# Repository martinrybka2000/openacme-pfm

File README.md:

# OpenACME‑PFM

**Open** **AC** **M**ains **E**nergy — **PFM** (Power Factor Meter).

An open-source **power quality meter** for AC installations. It measures voltage, current, power (active / reactive / apparent), frequency, power factors and THD, and exposes the results over Ethernet and Modbus, with PQDIF export for professional analysis tools.

> ⚠️ **DANGER — MAINS VOLTAGE.**
> This project connects directly to 230 V AC mains. Building, flashing, testing or using it can **injure or kill you** and can **start a fire**. Read [`docs/user-guide/safety.md`](docs/user-guide/safety.md) before touching any hardware. You build and use everything here **entirely at your own risk**.

---

## Status

🚧 **V2.0 — under development.**

The V1.0 single-board prototype (the basis of my master's thesis) is preserved **as-is** in [`v1.0/`](v1.0/) for reference only — no cleanup, no support.

## What it measures

- RMS voltage and current (total and fundamental)
- Active `P`, reactive `Q`, non-active `N` and apparent `S` power
- Fundamental components `P1`, `Q1`, `S1`
- Power factors: `PF` (true), `DPF` (displacement), `DF` (distortion)
- `THD` of voltage and current
- Frequency and phase angle (SOGI-PLL grid synchronisation)
- 10-cycle aggregation window (IEC 61000-4-7), loosely aligned with IEC 61000-4-30 Class S (best-effort, not a certification target)

## Planned architecture (V2.0)

- **Two boards:** a reusable _control board_ (MCU, power, Ethernet/Modbus, HMI, SD) + swappable _measurement board_ (1-phase or 3-phase; shunt, CT or Rogowski). Exact KiCad split is TBD.
- **Isolated sigma-delta** acquisition at high sample rates.
- **Comms:** Modbus TCP, Modbus RTU/RS485, PQDIF (IEEE 1159.3). WiFi is a separate board variant with an ESP instead of the STM32.
- **Power:** 24 V DC on the control board, USB-C for configuration, or transformer-fed from the measured phase (option).
- **Mechanical:** DIN-rail enclosure.
- **Measurements:** FFT and other power-quality parameters (voltage dips/swells, flicker).

## Repository layout

```
docs/          Requirements, architecture (ADRs), protocol specs, user guide
hardware/      KiCad projects (control-board, measurement-board) + enclosure
firmware/      Embedded C (STM32 via CubeMX/CMake; ESP32 WiFi variant)
software/      Desktop configuration app (Modbus)
tools/         Calibration and data-processing scripts
v1.0/          Legacy V1.0 prototype + master's thesis (reference dump)
```

## Getting started

See [`docs/user-guide/building.md`](docs/user-guide/building.md) for build/flash instructions and [`docs/requirements/requirements.md`](docs/requirements/requirements.md) for the current feature set.

## Documentation

- [Requirements](docs/requirements/requirements.md)
- [Roadmap](docs/roadmap.md)
- [System overview](docs/architecture/system-overview.md)
- [Architecture Decision Records](docs/architecture/adr/)
- [Protocol / Modbus map](docs/protocol/modbus-map.md)

## License

This project uses **strong copyleft** licences — if you use it, you must keep your derivatives open:

| Component                            | Licence                            | File               |
| ------------------------------------ | ---------------------------------- | ------------------ |
| Firmware & software                  | [GPL-3.0](LICENSE)                 | `LICENSE`          |
| Hardware (KiCad, Gerbers, enclosure) | [CERN-OHL-S-2.0](hardware/LICENSE) | `hardware/LICENSE` |
| Documentation                        | [CC-BY-SA-4.0](docs/LICENSE)       | `docs/LICENSE`     |

See [CONTRIBUTING.md](CONTRIBUTING.md) and [SECURITY.md](SECURITY.md).

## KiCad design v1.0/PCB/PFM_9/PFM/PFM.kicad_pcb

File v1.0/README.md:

# V1.0 — legacy prototype (reference only)

This directory is the home for the **unorganized dump** of the V1.0 work, kept for reference:

- The master's thesis as PDF (Polish and English).
- The V1.0 KiCad project (`PCB/`), firmware (`Firmware_VSCode/`) and measurement data (`pomiary/`).
- Serial Studio project files (`Serial_studio_proj/`).
- Third-party libraries used by V1.0 (`scpi-parser-master/`).

**No cleanup, no support.** These files are historical reference; active development happens at the repository root (V2.0).

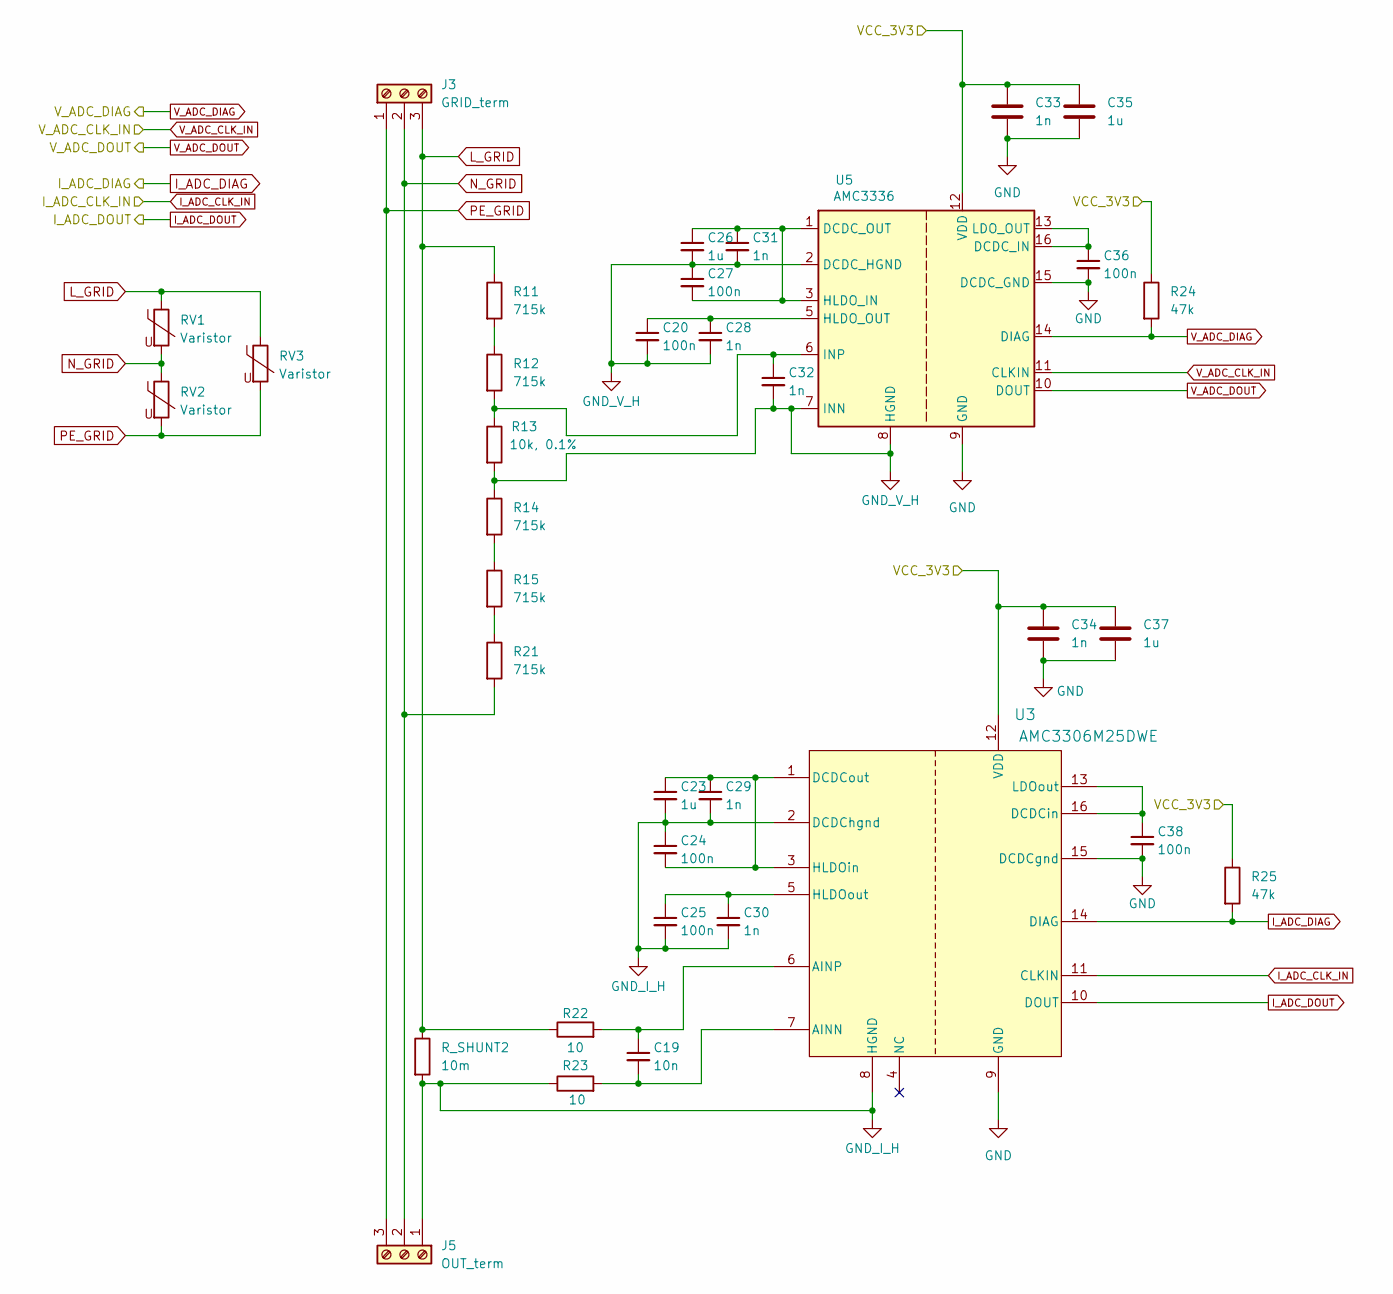
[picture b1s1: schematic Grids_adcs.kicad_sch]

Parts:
C19: 10n; C_0603_1608Metric_Pad1.08x0.95mm_HandSolder
C20, C25: 100n; C_1206_3216Metric_Pad1.33x1.80mm_HandSolder
C23, C26: 1u; C_0603_1608Metric_Pad1.08x0.95mm_HandSolder
C24, C27, C36, C38: 100n; C_0603_1608Metric_Pad1.08x0.95mm_HandSolder
C28, C30, C33, C34: 1n; C_1206_3216Metric_Pad1.33x1.80mm_HandSolder
C29, C31, C32: 1n; C_0603_1608Metric_Pad1.08x0.95mm_HandSolder
C35, C37: 1u; C_1206_3216Metric_Pad1.33x1.80mm_HandSolder
J3: GRID_term; TerminalBlock_Altech_AK300-3_P5.00mm
J5: OUT_term; TerminalBlock_Altech_AK300-3_P5.00mm
R11, R12, R14, R15, R21: 715k; R_0805_2012Metric_Pad1.20x1.40mm_HandSolder
R13: 10k, 0.1%; R_0603_1608Metric_Pad0.98x0.95mm_HandSolder
R22, R23: 10; R_0603_1608Metric_Pad0.98x0.95mm_HandSolder
R24, R25: 47k; R_0603_1608Metric_Pad0.98x0.95mm_HandSolder
RV1, RV2, RV3: Varistor; R_4020_10251Metric_Pad1.65x5.30mm_HandSolder
R_SHUNT2: 10m; R_2512_6332Metric
U3: AMC3306M25DWE; DWE0016A-IPC_A
U5: AMC3336; SOIC-16W_7.5x10.3mm_P1.27mm

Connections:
/GRID_ADCs1/VCC_3V3: C33.1, C34.1, C35.1, C37.1, R24.1, R25.1, U3.12 (VDD), U5.12 (VDD); also elsewhere on the board
GND: C33.2, C34.2, C35.2, C36.2, C37.2, C38.2, U3.9 (GND), U3.15 (DCDCgnd), U5.9 (GND), U5.15 (DCDC_GND); also elsewhere on the board
GND_I_H: C23.2, C24.1, C25.2, C29.2, C30.2, J5.1, R23.1, R_SHUNT2.2, U3.2 (DCDChgnd), U3.8 (HGND)
GND_V_H: C20.2, C26.2, C27.1, C28.2, C31.2, C32.2, R13.2, R14.1, U5.2 (DCDC_HGND), U5.7 (INN), U5.8 (HGND)
I_ADC_CLK_IN: U3.11 (CLKIN); also elsewhere on the board
I_ADC_DIAG: R25.2, U3.14 (DIAG); also elsewhere on the board
I_ADC_DOUT: U3.10 (DOUT); also elsewhere on the board
L_GRID: J3.3, R11.1, R22.1, RV1.1, RV3.1, R_SHUNT2.1
N_GRID: J3.2, J5.2, R21.2, RV1.2, RV2.1
unnamed: R11.2, R12.1
unnamed: R14.2, R15.1
unnamed: R15.2, R21.1
unnamed: C19.2, R23.2, U3.7 (AINN)
unnamed: C19.1, R22.2, U3.6 (AINP)
unnamed: C38.1, U3.13 (LDOout), U3.16 (DCDCin)
unnamed: C23.1, C24.2, C29.1, U3.1 (DCDCout), U3.3 (HLDOin)
unnamed: C25.1, C30.1, U3.5 (HLDOout)
unnamed: C36.1, U5.13 (LDO_OUT), U5.16 (DCDC_IN)
unnamed: C26.1, C27.2, C31.1, U5.1 (DCDC_OUT), U5.3 (HLDO_IN)
unnamed: C20.1, C28.1, U5.5 (HLDO_OUT)
unnamed: C32.1, R12.2, R13.1, U5.6 (INP)
PE_GRID: J3.1, J5.3, RV2.2, RV3.2
V_ADC_CLK_IN: U5.11 (CLKIN); also elsewhere on the board
V_ADC_DIAG: R24.2, U5.14 (DIAG); also elsewhere on the board
V_ADC_DOUT: U5.10 (DOUT); also elsewhere on the board

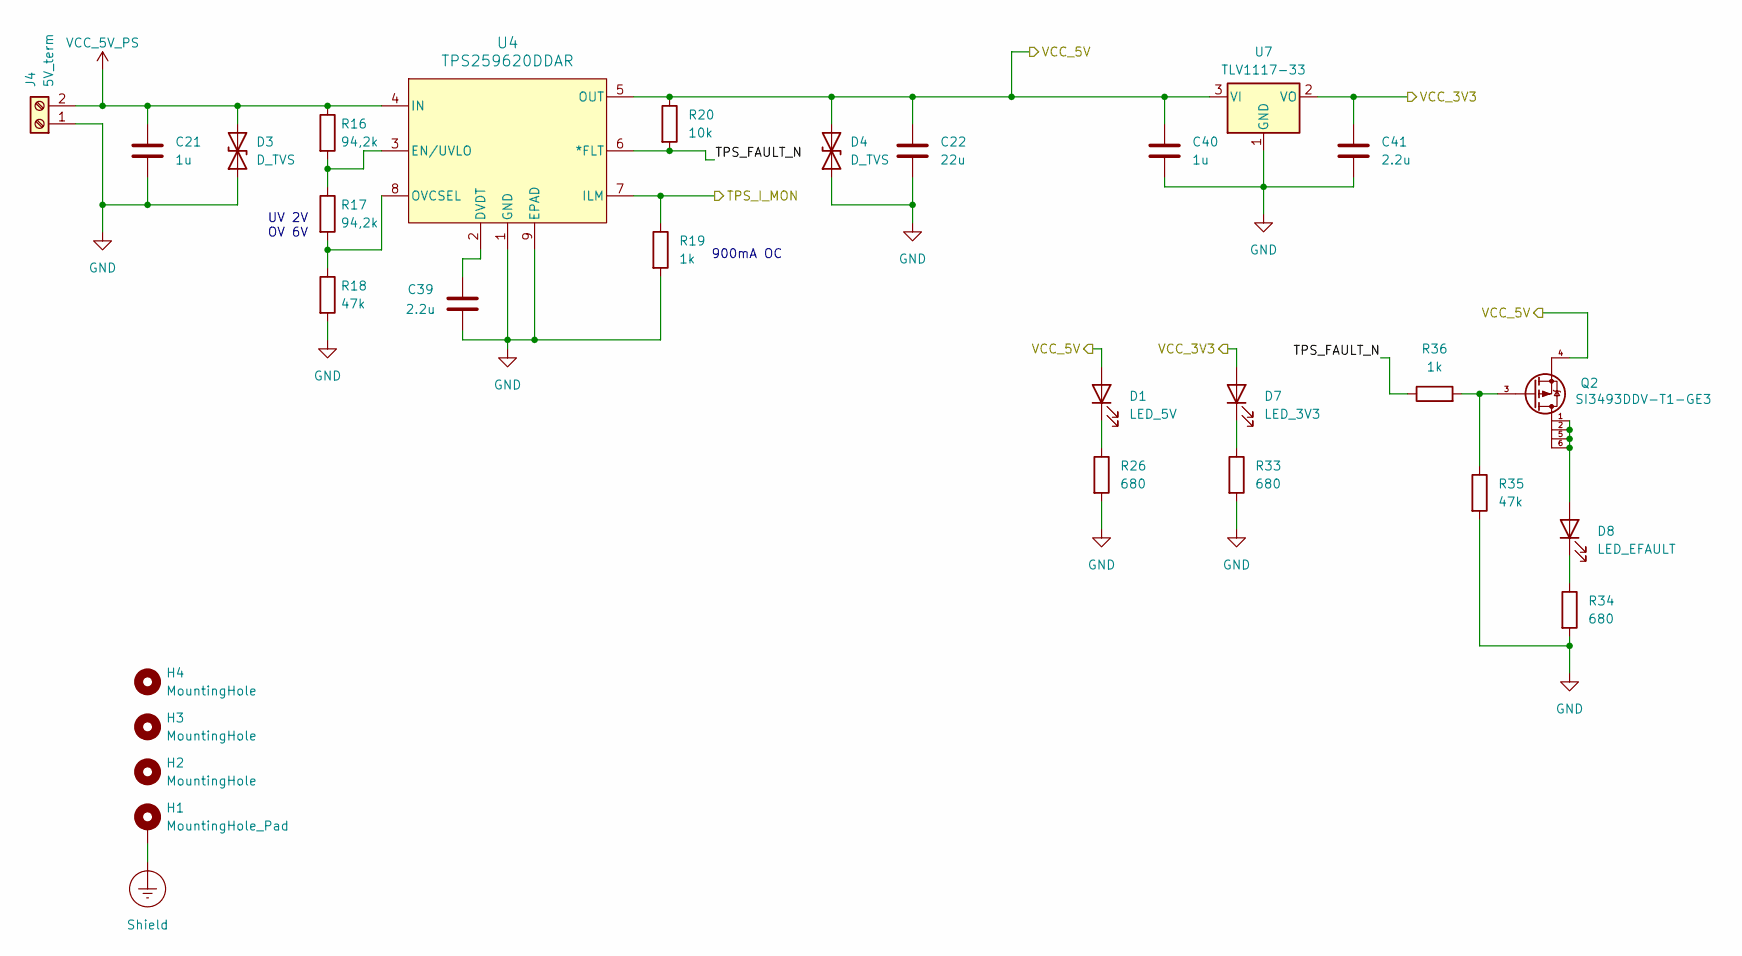
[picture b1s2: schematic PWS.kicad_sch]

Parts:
C21, C40: 1u; C_1206_3216Metric_Pad1.33x1.80mm_HandSolder
C22: 22u; C_1206_3216Metric_Pad1.33x1.80mm_HandSolder
C39, C41: 2.2u; C_0603_1608Metric_Pad1.08x0.95mm_HandSolder
D1: LED_5V; LED_0805_2012Metric_Pad1.15x1.40mm_HandSolder
D3: D_TVS; D_0603_1608Metric_Pad1.05x0.95mm_HandSolder
D4: D_TVS; D_0402_1005Metric_Pad0.77x0.64mm_HandSolder
D7: LED_3V3; LED_0805_2012Metric_Pad1.15x1.40mm_HandSolder
D8: LED_EFAULT; LED_0805_2012Metric_Pad1.15x1.40mm_HandSolder
H1: MountingHole_Pad; MountingHole_4.3mm_M4_DIN965_Pad_TopBottom
H2, H3, H4: MountingHole; MountingHole_4mm
J4: 5V_term; TerminalBlock_Altech_AK300-2_P5.00mm
Q2: SI3493DDV-T1-GE3; SOT95P284X110-6N; Mouser Part Number 78-SI3493DDV-T1-GE3
R16, R17: 94,2k; R_0603_1608Metric_Pad0.98x0.95mm_HandSolder
R18, R35: 47k; R_0603_1608Metric_Pad0.98x0.95mm_HandSolder
R19, R36: 1k; R_0603_1608Metric_Pad0.98x0.95mm_HandSolder
R20: 10k; R_0603_1608Metric_Pad0.98x0.95mm_HandSolder
R26, R33, R34: 680; R_0603_1608Metric_Pad0.98x0.95mm_HandSolder
U4: TPS259620DDAR; SOIC_20DDAR_TEX
U7: TLV1117-33; SOT-223-3_TabPin2

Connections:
/GRID_ADCs1/VCC_3V3: C41.1, D7.2 (A), U7.2 (VO); also elsewhere on the board
/Power supply1/TPS_FAULT_N: R20.2, R36.1, U4.6 (*FLT)
/Power supply1/TPS_I_MON: R19.1, U4.7 (ILM); also elsewhere on the board
/Power supply1/VCC_5V: C22.1, C40.1, D1.2 (A), D4.2 (A2), Q2.4, R20.1, U4.5 (OUT), U7.3 (VI)
GND: C21.2, C22.2, C39.2, C40.2, C41.2, D3.1 (A1), D4.1 (A1), J4.1, R18.2, R19.2, R26.2, R33.2, R34.2, R35.2, U4.1 (GND), U4.9 (EPAD), U7.1 (GND); also elsewhere on the board
unnamed: D1.1 (K), R26.1
unnamed: D7.1 (K), R33.1
unnamed: D8.2 (A), Q2.1, Q2.2, Q2.5, Q2.6
unnamed: D8.1 (K), R34.1
unnamed: Q2.3, R35.1, R36.2
unnamed: C39.1, U4.2 (DVDT)
unnamed: R16.2, R17.1, U4.3 (EN/UVLO)
unnamed: R17.2, R18.1, U4.8 (OVCSEL)
Shield: H1.1; also elsewhere on the board
VCC_5V_PS: C21.1, D3.2 (A2), J4.2, R16.1, U4.4 (IN)

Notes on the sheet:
900mA OC
UV 2V OV 6V

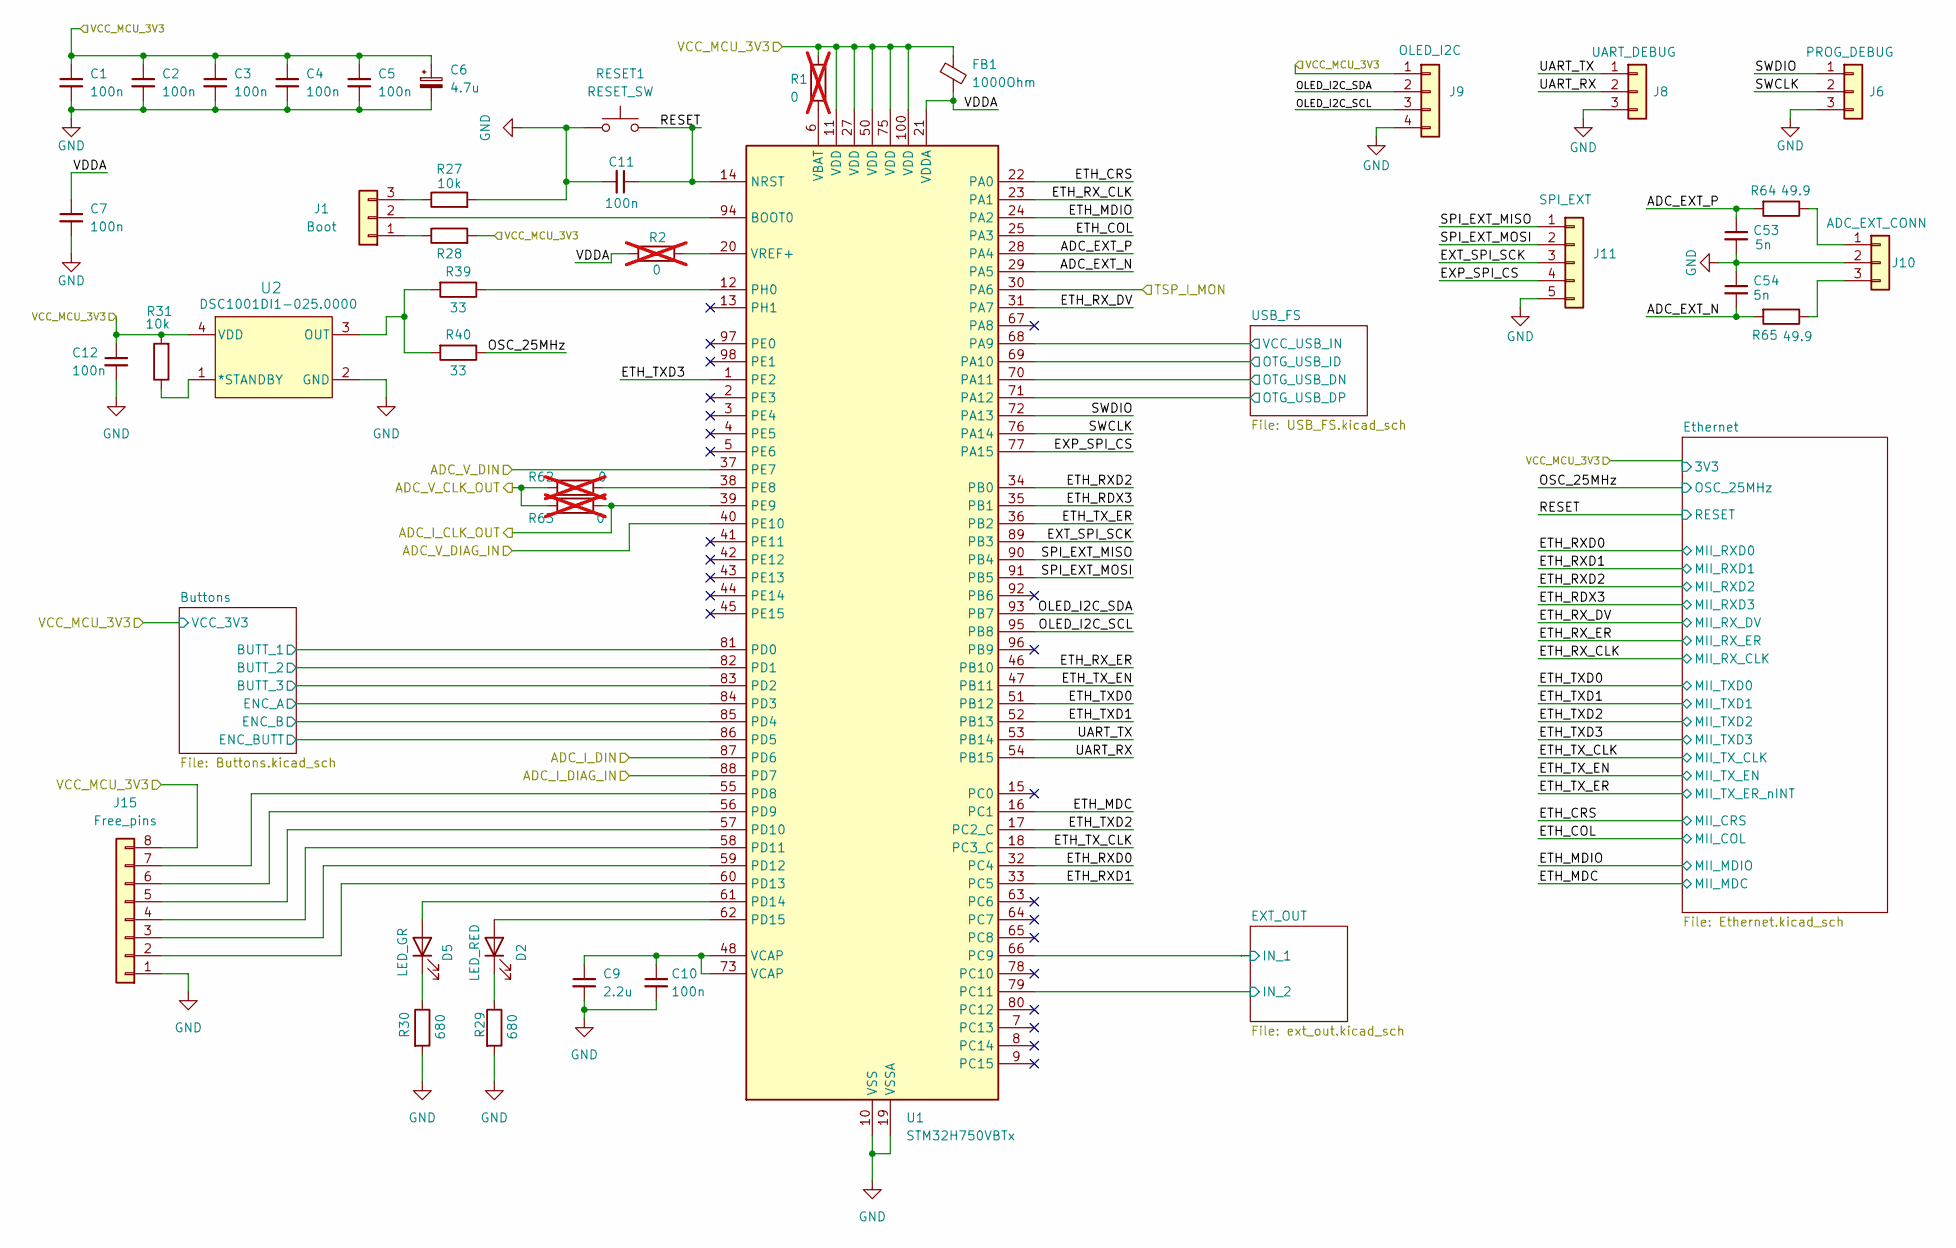
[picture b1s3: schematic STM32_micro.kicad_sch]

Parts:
C1, C2, C3, C4, C5, C7, C10, C11, C12: 100n; C_0603_1608Metric_Pad1.08x0.95mm_HandSolder
C6: 4.7u; C_0805_2012Metric_Pad1.18x1.45mm_HandSolder
C9: 2.2u; C_0603_1608Metric_Pad1.08x0.95mm_HandSolder
C53, C54: 5n; C_0805_2012Metric
D2: LED_RED; LED_0805_2012Metric_Pad1.15x1.40mm_HandSolder
D5: LED_GR; LED_0805_2012Metric_Pad1.15x1.40mm_HandSolder
FB1: 1000Ohm; L_0603_1608Metric_Pad1.05x0.95mm_HandSolder
J1: Boot; PinHeader_1x03_P2.54mm_Vertical
J6: PROG_DEBUG; PinHeader_1x03_P2.54mm_Vertical
J8: UART_DEBUG; PinHeader_1x03_P2.54mm_Vertical
J9: OLED_I2C; JST_XH_B4B-XH-AM_1x04_P2.50mm_Vertical
J10: ADC_EXT_CONN; FanPinHeader_1x03_P2.54mm_Vertical
J11: SPI_EXT; JST_XH_B5B-XH-AM_1x05_P2.50mm_Vertical
J15: Free_pins; JST_XH_B8B-XH-AM_1x08_P2.50mm_Vertical
R1, R2: 0; R_0402_1005Metric; not fitted
R27, R28, R31: 10k; R_0603_1608Metric_Pad0.98x0.95mm_HandSolder
R29, R30: 680; R_0603_1608Metric_Pad0.98x0.95mm_HandSolder
R39, R40: 33; R_0603_1608Metric_Pad0.98x0.95mm_HandSolder
R62, R63: 0; R_0402_1005Metric_Pad0.72x0.64mm_HandSolder; not fitted
R64, R65: 49.9; R_0402_1005Metric_Pad0.72x0.64mm_HandSolder
RESET1: RESET_SW; SW_DIP_SPSTx01_Slide_9.78x4.72mm_W8.61mm_P2.54mm
U1: STM32H750VBTx; LQFP-100_14x14mm_P0.5mm
U2: DSC1001DI1-025.0000; CDFN4_2P5X2_MCH

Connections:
/GRID_ADCs1/VCC_3V3: C1.1, C2.1, C3.1, C4.1, C5.1, C6.1, C12.1, FB1.1, J9.1, J15.8, R1.1, R28.2, R31.2, U1.11 (VDD), U1.27 (VDD), U1.50 (VDD), U1.75 (VDD), U1.100 (VDD), U2.4 (VDD); also elsewhere on the board
/Power supply1/TPS_I_MON: U1.30 (PA6); also elsewhere on the board
/STM33/ADC_EXT_N: C54.2, R65.2, U1.29 (PA5)
/STM33/ADC_EXT_P: C53.1, R64.2, U1.28 (PA4)
/STM33/Buttons/BUTT_1: U1.81 (PD0); also elsewhere on the board
/STM33/Buttons/BUTT_2: U1.82 (PD1); also elsewhere on the board
/STM33/Buttons/BUTT_3: U1.83 (PD2); also elsewhere on the board
/STM33/Buttons/ENC_A: U1.84 (PD3); also elsewhere on the board
/STM33/Buttons/ENC_B: U1.85 (PD4); also elsewhere on the board
/STM33/Buttons/ENC_BUTT: U1.86 (PD5); also elsewhere on the board
/STM33/ETH_COL: U1.25 (PA3); also elsewhere on the board
/STM33/ETH_CRS: U1.22 (PA0); also elsewhere on the board
/STM33/ETH_MDC: U1.16 (PC1); also elsewhere on the board
/STM33/ETH_MDIO: U1.24 (PA2); also elsewhere on the board
/STM33/ETH_RDX3: U1.35 (PB1); also elsewhere on the board
/STM33/ETH_RXD0: U1.32 (PC4); also elsewhere on the board
/STM33/ETH_RXD1: U1.33 (PC5); also elsewhere on the board
/STM33/ETH_RXD2: U1.34 (PB0); also elsewhere on the board
/STM33/ETH_RX_CLK: U1.23 (PA1); also elsewhere on the board
/STM33/ETH_RX_DV: U1.31 (PA7); also elsewhere on the board
/STM33/ETH_RX_ER: U1.46 (PB10); also elsewhere on the board
/STM33/ETH_TXD0: U1.51 (PB12); also elsewhere on the board
/STM33/ETH_TXD1: U1.52 (PB13); also elsewhere on the board
/STM33/ETH_TXD2: U1.17 (PC2_C); also elsewhere on the board
/STM33/ETH_TXD3: U1.1 (PE2); also elsewhere on the board
/STM33/ETH_TX_CLK: U1.18 (PC3_C); also elsewhere on the board
/STM33/ETH_TX_EN: U1.47 (PB11); also elsewhere on the board
/STM33/ETH_TX_ER: U1.36 (PB2); also elsewhere on the board
/STM33/EXP_SPI_CS: J11.4, U1.77 (PA15)
/STM33/EXT_OUT/IN_1: U1.66 (PC9); also elsewhere on the board
/STM33/EXT_OUT/IN_2: U1.79 (PC11); also elsewhere on the board
/STM33/EXT_SPI_SCK: J11.3, U1.89 (PB3)
/STM33/OLED_I2C_SCL: J9.3, U1.95 (PB8)
/STM33/OLED_I2C_SDA: J9.2, U1.93 (PB7)
/STM33/OSC_25MHz: R40.1; also elsewhere on the board
/STM33/RESET: C11.1, RESET1.2, U1.14 (NRST); also elsewhere on the board
/STM33/SPI_EXT_MISO: J11.1, U1.90 (PB4)
/STM33/SPI_EXT_MOSI: J11.2, U1.91 (PB5)
/STM33/SWCLK: J6.2, U1.76 (PA14)
/STM33/SWDIO: J6.1, U1.72 (PA13)
/STM33/UART_RX: J8.2, U1.54 (PB15)
/STM33/UART_TX: J8.1, U1.53 (PB14)
/STM33/USB_FS/OTG_USB_DN: U1.70 (PA11); also elsewhere on the board
/STM33/USB_FS/OTG_USB_DP: U1.71 (PA12); also elsewhere on the board
/STM33/USB_FS/OTG_USB_ID: U1.69 (PA10); also elsewhere on the board
/STM33/USB_FS/VCC_USB_IN: U1.68 (PA9); also elsewhere on the board
/STM33/VDDA: C7.1, FB1.2, R2.1, U1.21 (VDDA)
GND: C1.2, C2.2, C3.2, C4.2, C5.2, C6.2, C7.2, C9.2, C10.2, C11.2, C12.2, C53.2, C54.1, J6.3, J8.3, J9.4, J10.2, J11.5, J15.1, R27.2, R29.2, R30.2, RESET1.1, U1.10 (VSS), U1.19 (VSSA), U1.26 (VSS), U1.49 (VSS), U1.74 (VSS), U1.99 (VSS), U2.2 (GND); also elsewhere on the board
I_ADC_CLK_IN: R63.1, U1.39 (PE9); also elsewhere on the board
I_ADC_DIAG: U1.88 (PD7); also elsewhere on the board
I_ADC_DOUT: U1.87 (PD6); also elsewhere on the board
unnamed: C9.1, C10.1, U1.48 (VCAP), U1.73 (VCAP)
unnamed: D2.2 (A), U1.62 (PD15)
unnamed: D2.1 (K), R29.1
unnamed: D5.2 (A), U1.61 (PD14)
unnamed: D5.1 (K), R30.1
unnamed: J1.1, R28.1
unnamed: J1.2, U1.94 (BOOT0)
unnamed: J1.3, R27.1
unnamed: J10.1, R64.1
unnamed: J10.3, R65.1
unnamed: J15.2, U1.60 (PD13)
unnamed: J15.3, U1.59 (PD12)
unnamed: J15.4, U1.58 (PD11)
unnamed: J15.5, U1.57 (PD10)
unnamed: J15.6, U1.56 (PD9)
unnamed: J15.7, U1.55 (PD8)
unnamed: R62.1, U1.38 (PE8)
unnamed: R39.1, U1.12 (PH0)
unnamed: R1.2, U1.6 (VBAT)
unnamed: R2.2, U1.20 (VREF+)
unnamed: R31.1, U2.1 (*STANDBY)
unnamed: R39.2, R40.2, U2.3 (OUT)
V_ADC_CLK_IN: R62.2, R63.2; also elsewhere on the board
V_ADC_DIAG: U1.40 (PE10); also elsewhere on the board
V_ADC_DOUT: U1.37 (PE7); also elsewhere on the board

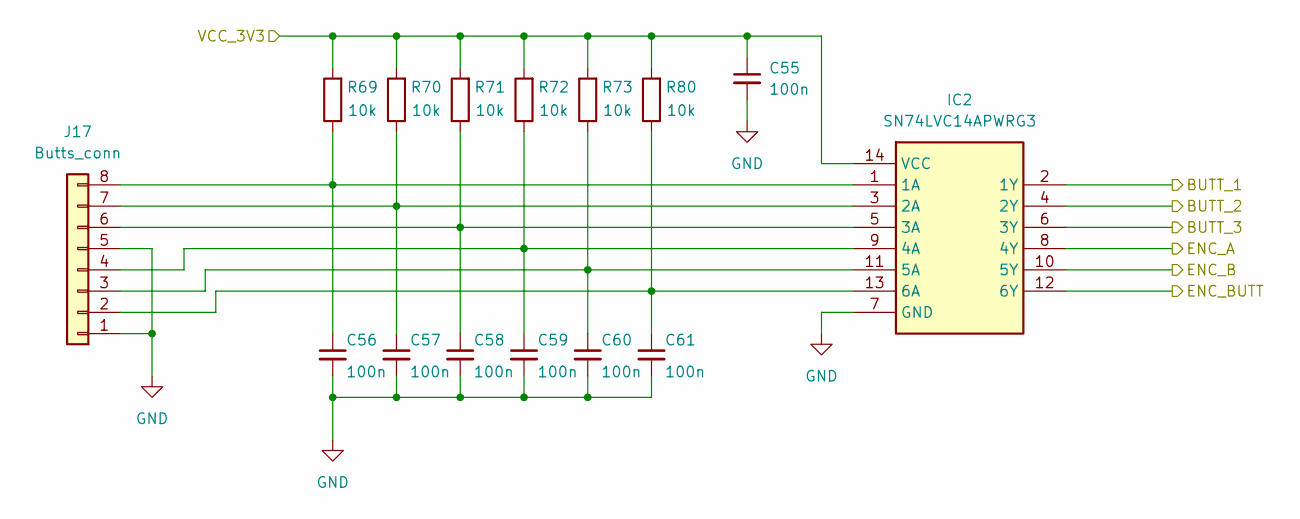
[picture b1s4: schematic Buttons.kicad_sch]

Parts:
C55, C56, C57, C58, C59, C60, C61: 100n; C_0603_1608Metric_Pad1.08x0.95mm_HandSolder
IC2: SN74LVC14APWRG3; SOP65P640X120-14N; Mouser Part Number 595-SN74LVC14APWRG3
J17: Butts_conn; JST_XH_B8B-XH-AM_1x08_P2.50mm_Vertical
R69, R70, R71, R72, R73, R80: 10k; R_0603_1608Metric_Pad0.98x0.95mm_HandSolder

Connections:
/GRID_ADCs1/VCC_3V3: C55.1, IC2.14 (VCC), R69.2, R70.2, R71.2, R72.2, R73.2, R80.2; also elsewhere on the board
/STM33/Buttons/BUTT_1: IC2.2 (1Y); also elsewhere on the board
/STM33/Buttons/BUTT_2: IC2.4 (2Y); also elsewhere on the board
/STM33/Buttons/BUTT_3: IC2.6 (3Y); also elsewhere on the board
/STM33/Buttons/ENC_A: IC2.8 (4Y); also elsewhere on the board
/STM33/Buttons/ENC_B: IC2.10 (5Y); also elsewhere on the board
/STM33/Buttons/ENC_BUTT: IC2.12 (6Y); also elsewhere on the board
GND: C55.2, C56.2, C57.2, C58.2, C59.2, C60.2, C61.2, IC2.7 (GND), J17.1, J17.5; also elsewhere on the board
unnamed: C56.1, IC2.1 (1A), J17.8, R69.1
unnamed: C57.1, IC2.3 (2A), J17.7, R70.1
unnamed: C58.1, IC2.5 (3A), J17.6, R71.1
unnamed: C59.1, IC2.9 (4A), J17.4, R72.1
unnamed: C60.1, IC2.11 (5A), J17.3, R73.1
unnamed: C61.1, IC2.13 (6A), J17.2, R80.1

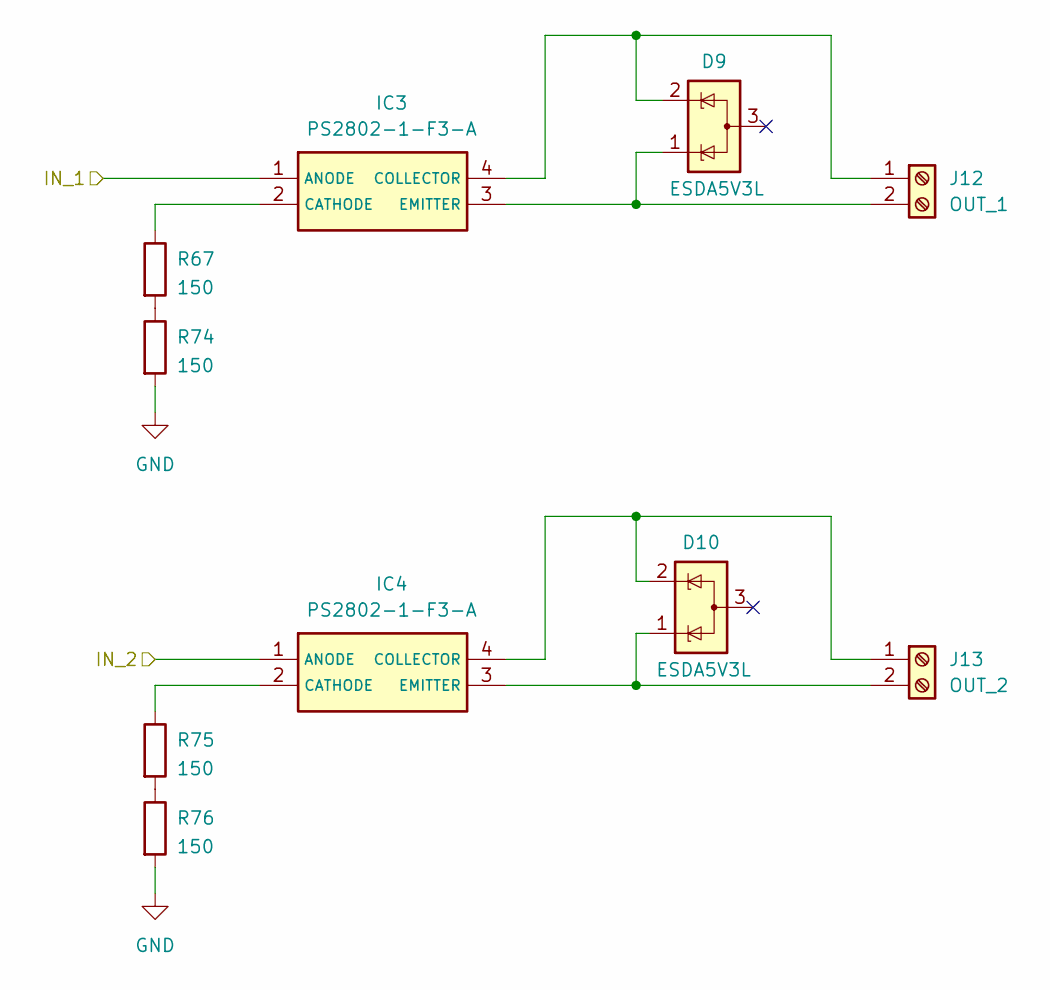
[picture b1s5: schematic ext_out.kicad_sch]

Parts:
D9, D10: ESDA5V3L; SOT-23-3
IC3, IC4: PS2802-1-F3-A; SOIC127P700X210-4N; Mouser Part Number 551-PS2802-1-F3-A
J12: OUT_1; TerminalBlock_Altech_AK300-2_P5.00mm
J13: OUT_2; TerminalBlock_Altech_AK300-2_P5.00mm
R67, R74, R75, R76: 150; R_0603_1608Metric_Pad0.98x0.95mm_HandSolder

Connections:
/STM33/EXT_OUT/IN_1: IC3.1 (ANODE); also elsewhere on the board
/STM33/EXT_OUT/IN_2: IC4.1 (ANODE); also elsewhere on the board
GND: R74.2, R76.2; also elsewhere on the board
unnamed: IC3.2 (CATHODE), R67.1
unnamed: D9.2 (K), IC3.4 (COLLECTOR), J12.1
unnamed: D9.1 (K), IC3.3 (EMITTER), J12.2
unnamed: IC4.2 (CATHODE), R75.1
unnamed: D10.2 (K), IC4.4 (COLLECTOR), J13.1
unnamed: D10.1 (K), IC4.3 (EMITTER), J13.2
unnamed: R67.2, R74.1
unnamed: R75.2, R76.1

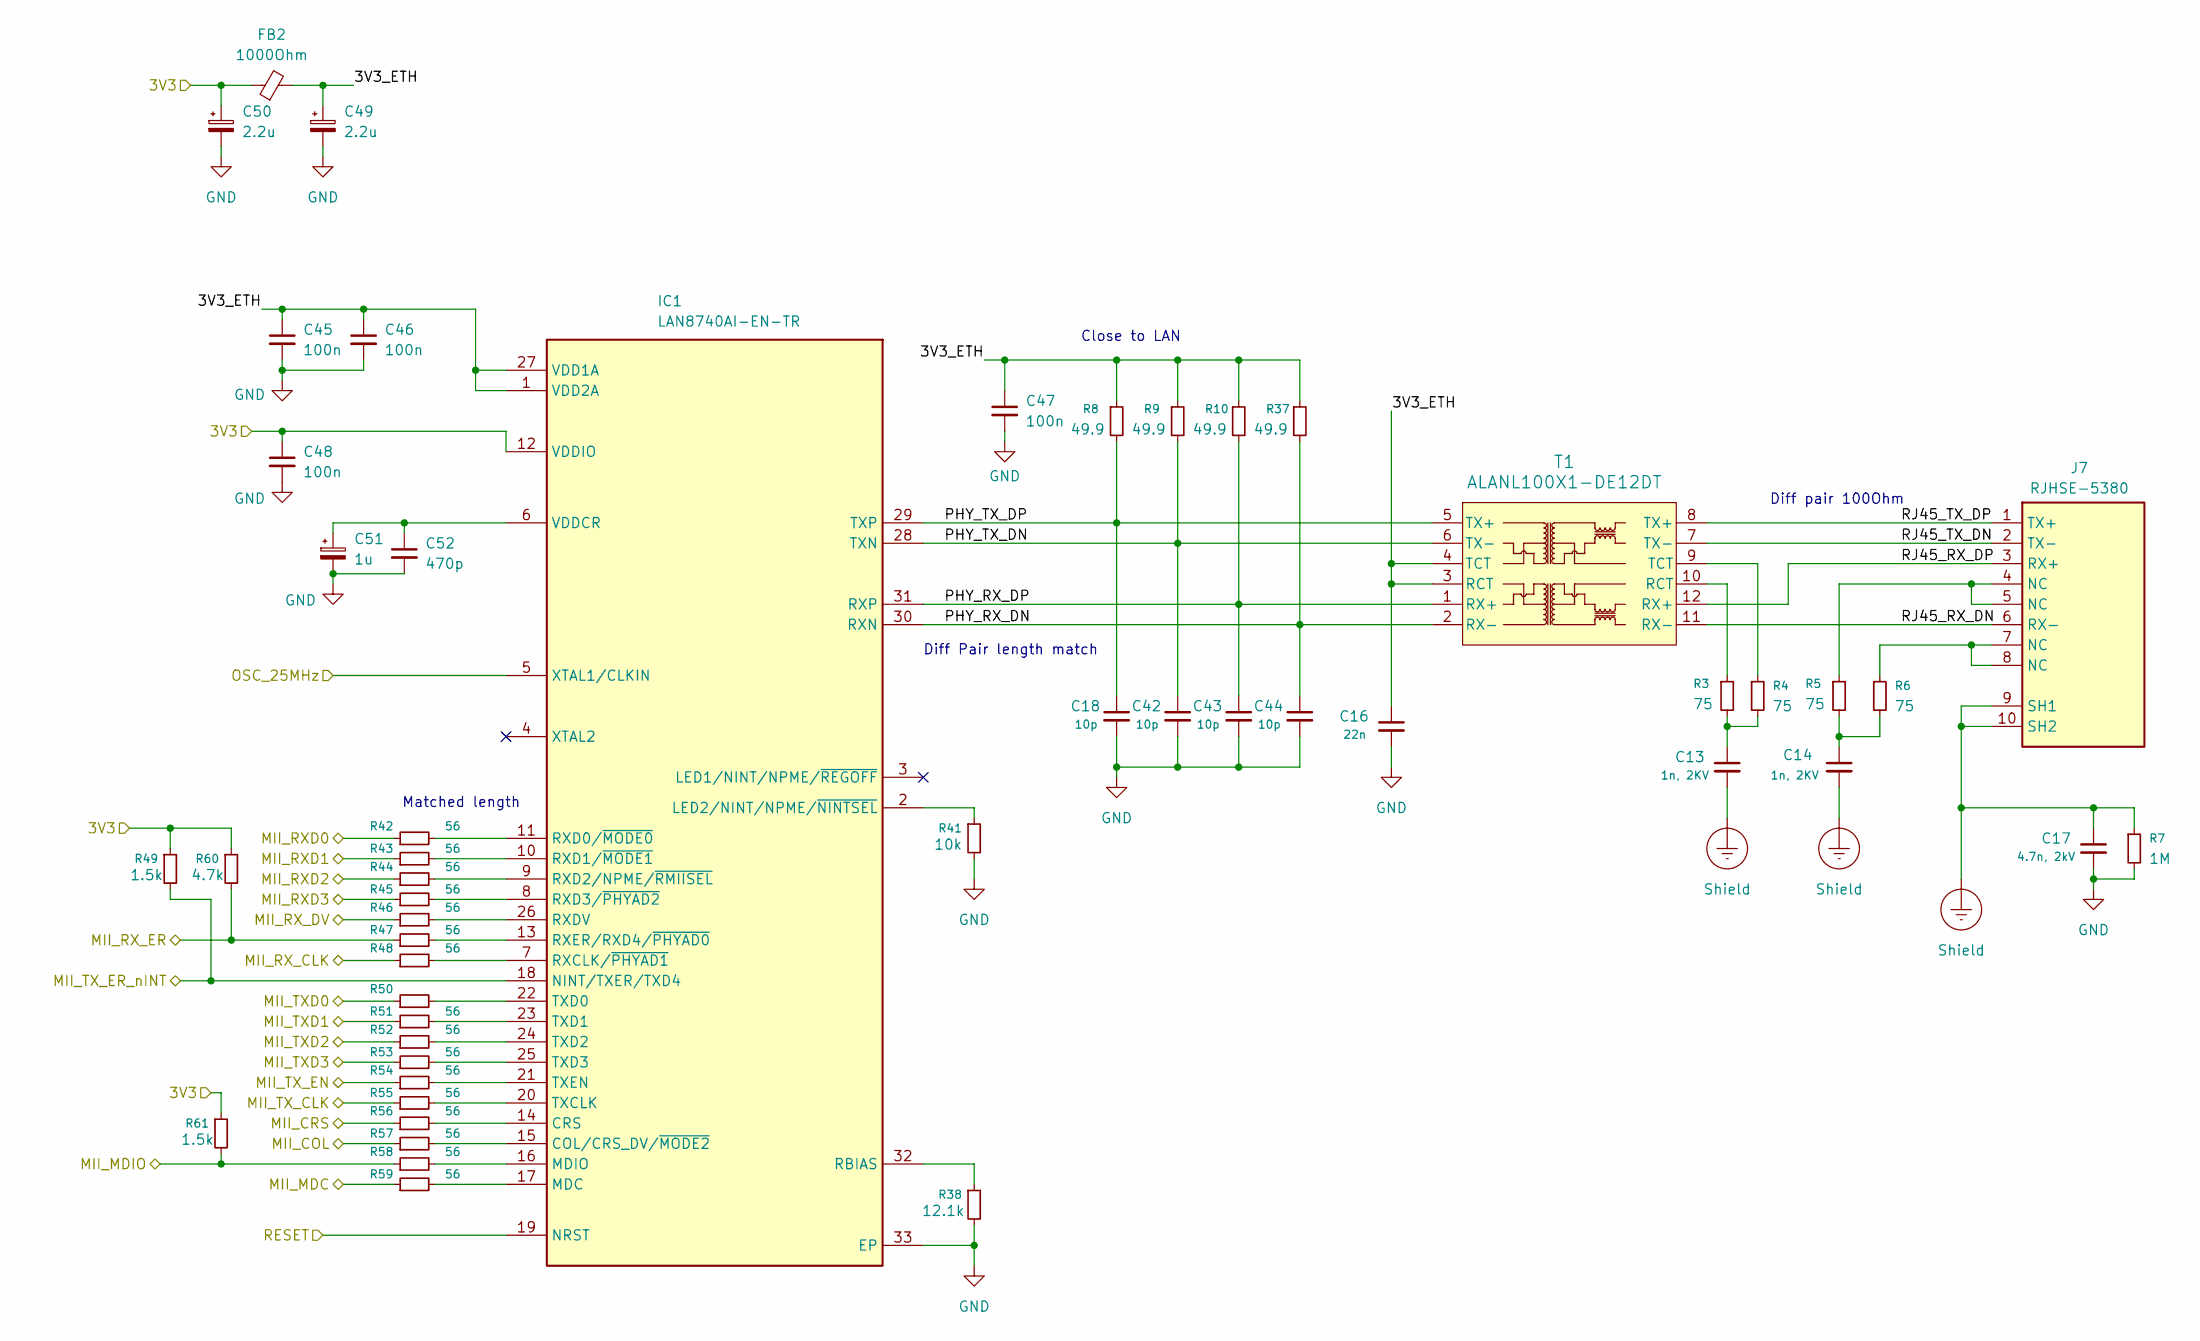
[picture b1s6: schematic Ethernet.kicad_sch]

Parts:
C13, C14: 1n, 2KV; C_1206_3216Metric_Pad1.33x1.80mm_HandSolder
C16: 22n; C_0402_1005Metric_Pad0.74x0.62mm_HandSolder
C17: 4.7n, 2kV; C_1210_3225Metric_Pad1.33x2.70mm_HandSolder
C18, C42, C43, C44: 10p; C_0402_1005Metric_Pad0.74x0.62mm_HandSolder
C45, C46, C48: 100n; C_0402_1005Metric
C47: 100n; C_0603_1608Metric_Pad1.08x0.95mm_HandSolder
C49, C50: 2.2u; C_0603_1608Metric_Pad1.08x0.95mm_HandSolder
C51: 1u; C_1206_3216Metric_Pad1.33x1.80mm_HandSolder
C52: 470p; C_0402_1005Metric
FB2: 1000Ohm; L_0603_1608Metric_Pad1.05x0.95mm_HandSolder
IC1: LAN8740AI-EN-TR; QFN50P500X500X100-33N-D; Mouser Part Number 579-LAN8740AI-EN-TR
J7: RJHSE-5380; RJ45_HALO_HFJ11-x2450HRL_Horizontal; Manufacturer_Part_Number RJHSE-5380
R3, R4, R5, R6: 75; R_0402_1005Metric_Pad0.72x0.64mm_HandSolder
R7: 1M; R_2512_6332Metric_Pad1.40x3.35mm_HandSolder
R8, R9, R10, R37: 49.9; R_0402_1005Metric_Pad0.72x0.64mm_HandSolder
R38: 12.1k; C_0603_1608Metric_Pad1.08x0.95mm_HandSolder
R41: 10k; R_0603_1608Metric_Pad0.98x0.95mm_HandSolder
R42, R43, R44, R45, R46, R47, R48, R56, R57, R58, R59: 56; R_0402_1005Metric
R49, R61: 1.5k; R_0402_1005Metric
R50, R51, R52, R53, R54, R55: 56; R_0402_1005Metric_Pad0.72x0.64mm_HandSolder
R60: 4.7k; R_0402_1005Metric
T1: ALANL100X1-DE12DT; SOIC12_ALANL100X1_ABR

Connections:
/GRID_ADCs1/VCC_3V3: C48.1, C50.1, FB2.1, IC1.12 (VDDIO), R49.1, R60.1, R61.1; also elsewhere on the board
/STM33/ETH_COL: R57.1; also elsewhere on the board
/STM33/ETH_CRS: R56.1; also elsewhere on the board
/STM33/ETH_MDC: R59.1; also elsewhere on the board
/STM33/ETH_MDIO: R58.1, R61.2; also elsewhere on the board
/STM33/ETH_RDX3: R45.1; also elsewhere on the board
/STM33/ETH_RXD0: R42.1; also elsewhere on the board
/STM33/ETH_RXD1: R43.1; also elsewhere on the board
/STM33/ETH_RXD2: R44.1; also elsewhere on the board
/STM33/ETH_RX_CLK: R48.1; also elsewhere on the board
/STM33/ETH_RX_DV: R46.1; also elsewhere on the board
/STM33/ETH_RX_ER: R47.1, R60.2; also elsewhere on the board
/STM33/ETH_TXD0: R50.1; also elsewhere on the board
/STM33/ETH_TXD1: R51.1; also elsewhere on the board
/STM33/ETH_TXD2: R52.1; also elsewhere on the board
/STM33/ETH_TXD3: R53.1; also elsewhere on the board
/STM33/ETH_TX_CLK: R55.1; also elsewhere on the board
/STM33/ETH_TX_EN: R54.1; also elsewhere on the board
/STM33/ETH_TX_ER: IC1.18 (NINT/TXER/TXD4), R49.2; also elsewhere on the board
/STM33/Ethernet/3V3_ETH: C16.1, C45.1, C46.1, C47.1, C49.1, FB2.2, IC1.1 (VDD2A), IC1.27 (VDD1A), R8.1, R9.1, R10.1, R37.1, T1.3 (RCT), T1.4 (TCT)
/STM33/Ethernet/PHY_RX_DN: C44.1, IC1.30 (RXN), R37.2, T1.2 (RX-)
/STM33/Ethernet/PHY_RX_DP: C43.1, IC1.31 (RXP), R10.2, T1.1 (RX+)
/STM33/Ethernet/PHY_TX_DN: C42.1, IC1.28 (TXN), R9.2, T1.6 (TX-)
/STM33/Ethernet/PHY_TX_DP: C18.1, IC1.29 (TXP), R8.2, T1.5 (TX+)
/STM33/Ethernet/RJ45_RX_DN: J7.6 (RX-), T1.11 (RX-)
/STM33/Ethernet/RJ45_RX_DP: J7.3 (RX+), T1.12 (RX+)
/STM33/Ethernet/RJ45_TX_DN: J7.2 (TX-), T1.7 (TX-)
/STM33/Ethernet/RJ45_TX_DP: J7.1 (TX+), T1.8 (TX+)
/STM33/OSC_25MHz: IC1.5 (XTAL1/CLKIN); also elsewhere on the board
/STM33/RESET: IC1.19 (NRST); also elsewhere on the board
GND: C16.2, C17.2, C18.2, C42.2, C43.2, C44.2, C45.2, C46.2, C47.2, C48.2, C49.2, C50.2, C51.2, C52.2, IC1.33 (EP), R7.2, R38.2, R41.2; also elsewhere on the board
unnamed: C13.1, R3.2, R4.2
unnamed: C14.1, R5.2, R6.2
unnamed: IC1.15 (COL/CRS_DV/~MODE2), R57.2
unnamed: IC1.14 (CRS), R56.2
unnamed: IC1.2 (LED2/NINT/NPME/~NINTSEL), R41.1
unnamed: IC1.17 (MDC), R59.2
unnamed: IC1.16 (MDIO), R58.2
unnamed: IC1.32 (RBIAS), R38.1
unnamed: IC1.7 (RXCLK/~PHYAD1), R48.2
unnamed: IC1.11 (RXD0/~MODE0), R42.2
unnamed: IC1.10 (RXD1/~MODE1), R43.2
unnamed: IC1.9 (RXD2/NPME/~RMIISEL), R44.2
unnamed: IC1.8 (RXD3/~PHYAD2), R45.2
unnamed: IC1.26 (RXDV), R46.2
unnamed: IC1.13 (RXER/RXD4/~PHYAD0), R47.2
unnamed: IC1.20 (TXCLK), R55.2
unnamed: IC1.22 (TXD0), R50.2
unnamed: IC1.23 (TXD1), R51.2
unnamed: IC1.24 (TXD2), R52.2
unnamed: IC1.25 (TXD3), R53.2
unnamed: IC1.21 (TXEN), R54.2
unnamed: C51.1, C52.1, IC1.6 (VDDCR)
unnamed: J7.4 (NC), J7.5 (NC), R5.1
unnamed: J7.7 (NC), J7.8 (NC), R6.1
unnamed: R3.1, T1.10 (RCT)
unnamed: R4.1, T1.9 (TCT)
Shield: C13.2, C14.2, C17.1, J7.9 (SH1), J7.10 (SH2), R7.1; also elsewhere on the board

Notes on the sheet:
Diff Pair length match
Matched length
Close to LAN
Diff pair 100Ohm

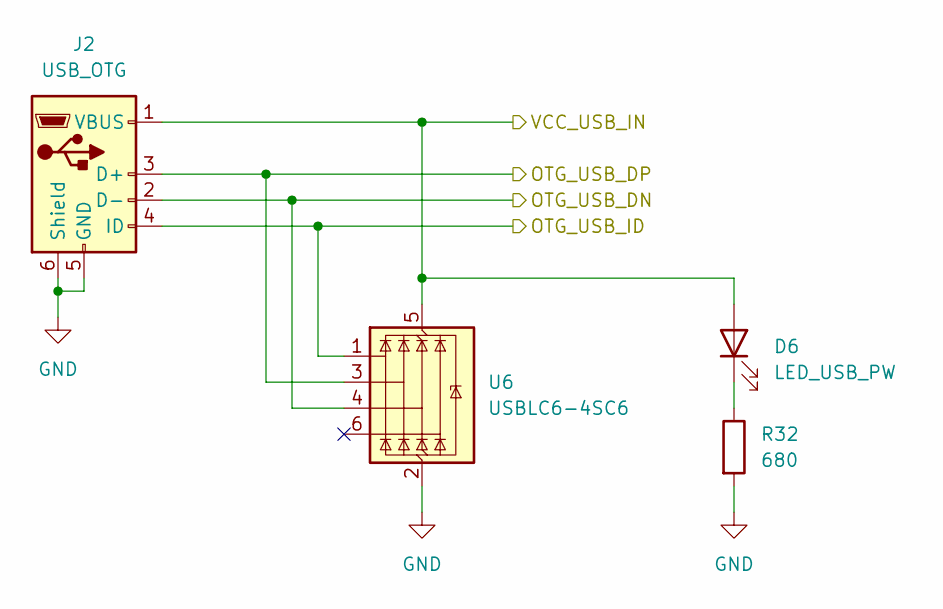
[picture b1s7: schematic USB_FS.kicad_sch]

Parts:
D6: LED_USB_PW; LED_0805_2012Metric_Pad1.15x1.40mm_HandSolder
J2: USB_OTG; USB_Micro-AB_Molex_47590-0001
R32: 680; R_0603_1608Metric_Pad0.98x0.95mm_HandSolder
U6: USBLC6-4SC6; SOT-23-6

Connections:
/STM33/USB_FS/OTG_USB_DN: J2.2 (D-), U6.4 (I/O3); also elsewhere on the board
/STM33/USB_FS/OTG_USB_DP: J2.3 (D+), U6.3 (I/O2); also elsewhere on the board
/STM33/USB_FS/OTG_USB_ID: J2.4 (ID), U6.1 (I/O1); also elsewhere on the board
/STM33/USB_FS/VCC_USB_IN: D6.2 (A), J2.1 (VBUS), U6.5 (VBUS); also elsewhere on the board
GND: J2.5 (GND), J2.6 (Shield), R32.2, U6.2 (GND); also elsewhere on the board
unnamed: D6.1 (K), R32.1
